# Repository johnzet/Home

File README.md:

# HomeAutomation
#test
#test master branch

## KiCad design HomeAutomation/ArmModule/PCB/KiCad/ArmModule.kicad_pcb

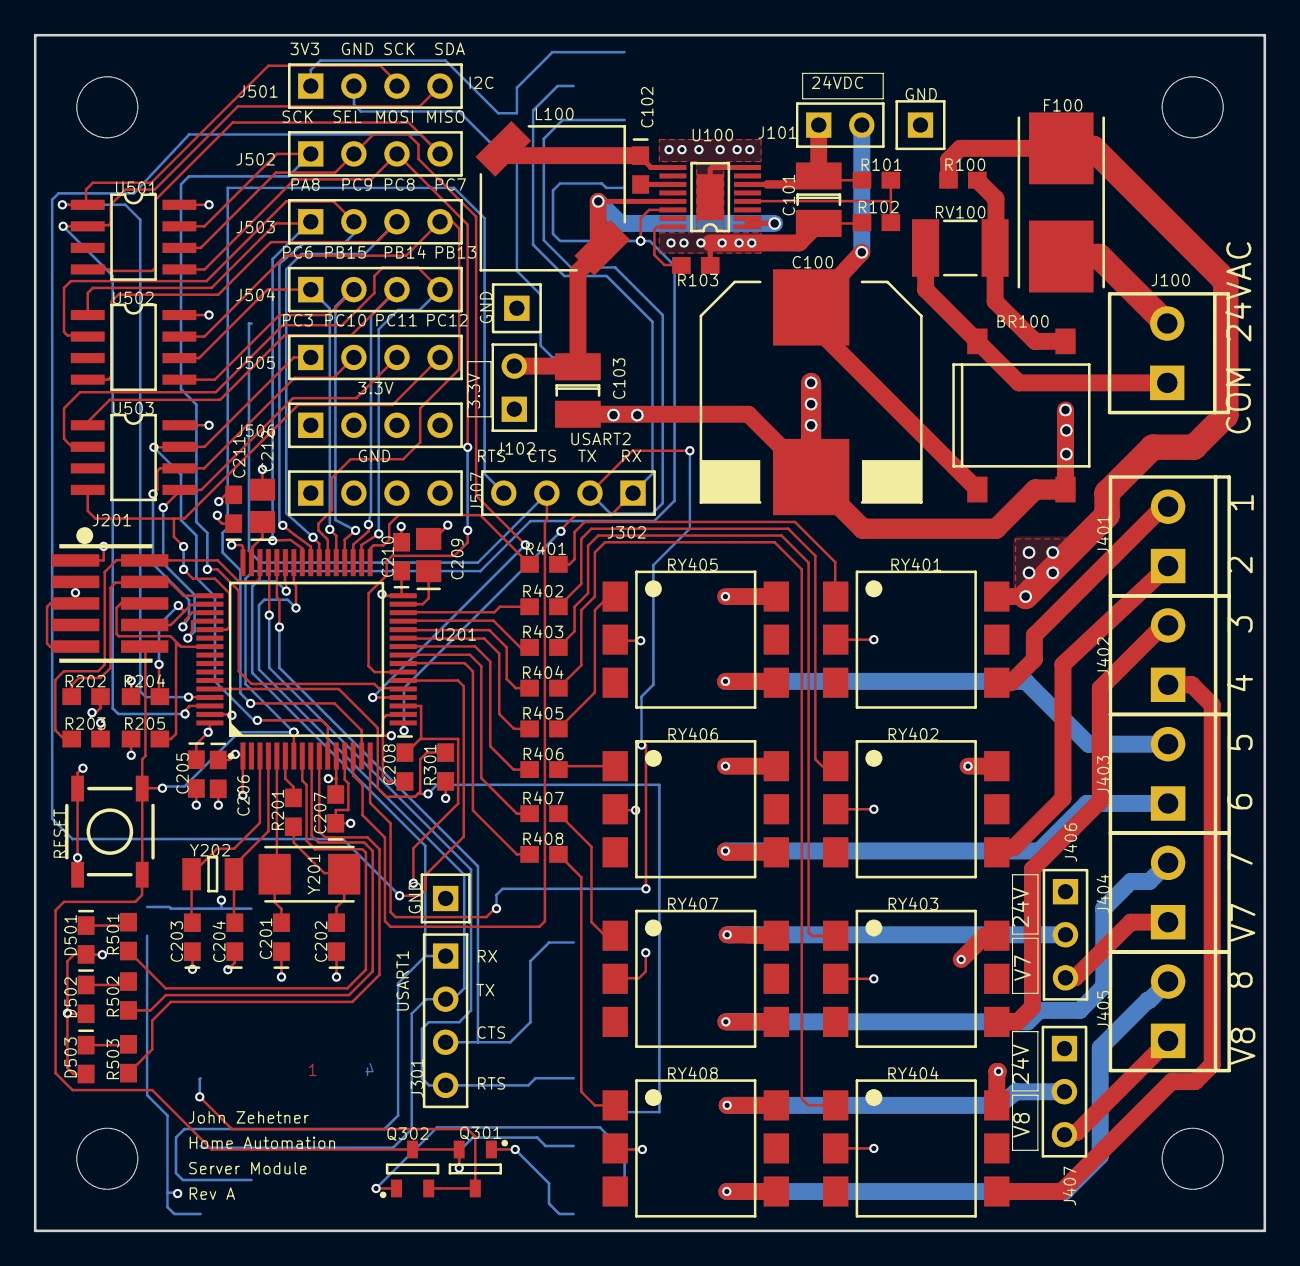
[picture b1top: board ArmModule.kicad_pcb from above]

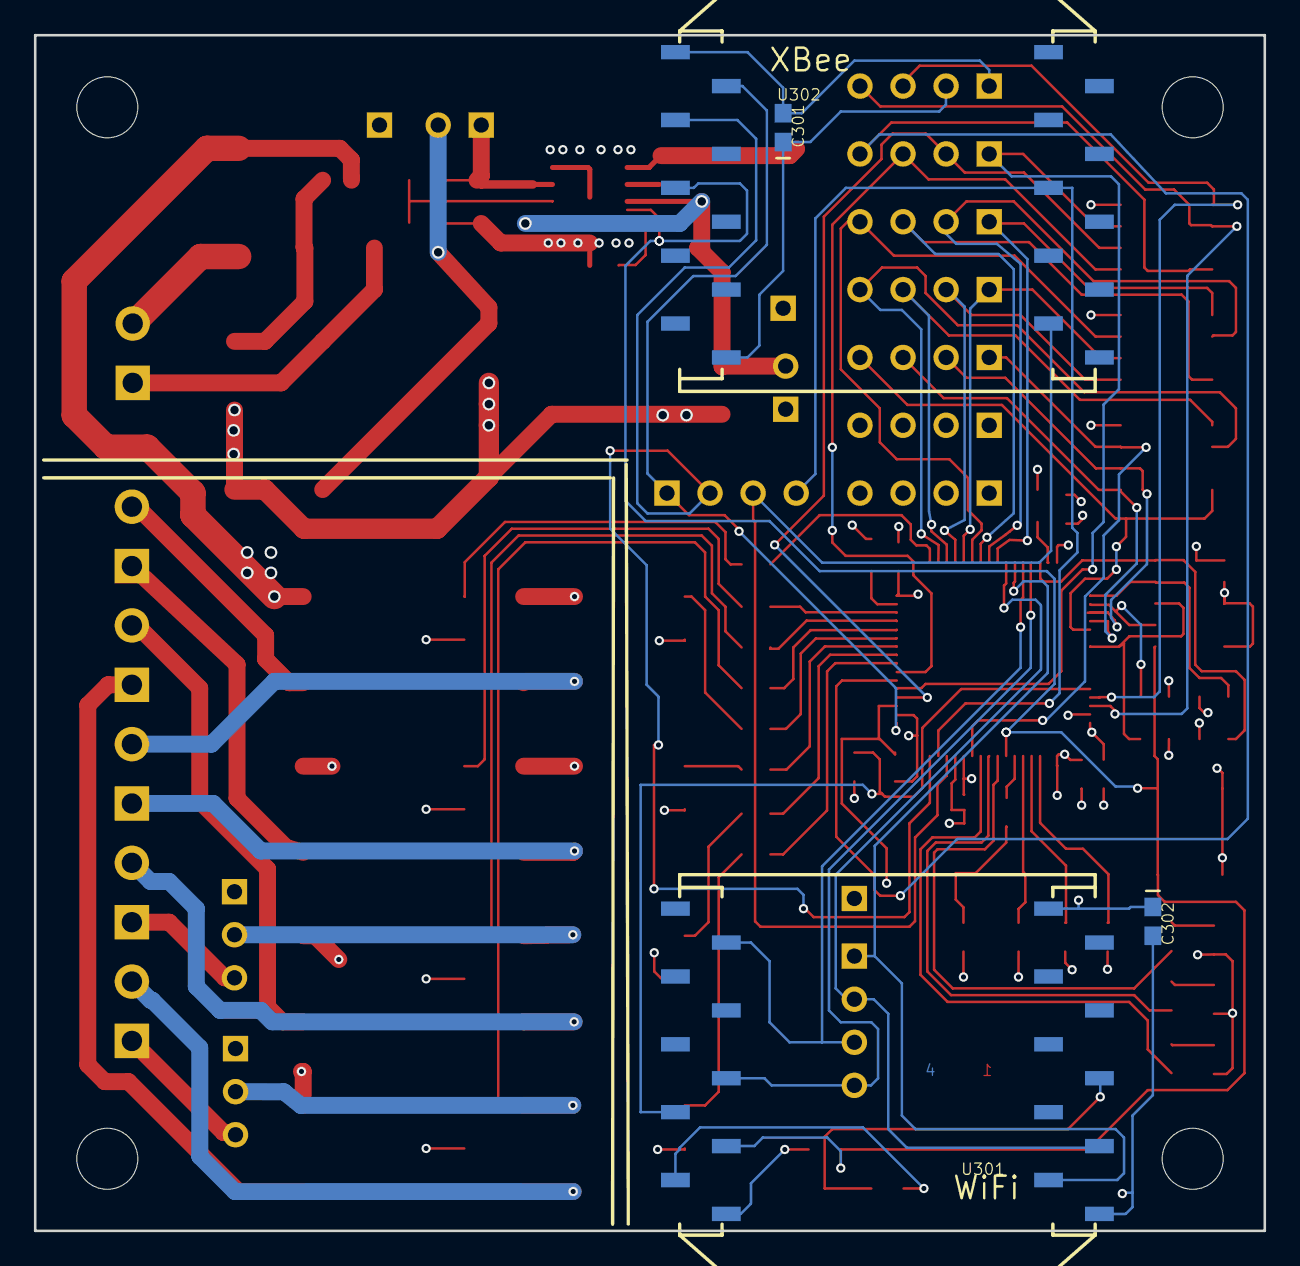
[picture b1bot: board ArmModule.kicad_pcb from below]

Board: 4 copper layers, 72.5 x 70.5 mm, 94 parts (4 on the bottom side), 89 nets.

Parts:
BR100: DF01S; Bridge_Rectifier
C100: 220uF 63V; Electro_Cap_H13
C101: 2.2u 100V; CAP_1210
C102: 0.22u; CAP_0603
C103: 22u; CAP_1210_C103
C201, C202: <= 26 pF; CAP_0603_C201
C203, C204: <= 5 pF; CAP_0603_C201
C205, C208: 100nF; CAP_0603_C205
C206: 100nF; CAP_0603_C206
C207, C210: 100nF; CAP_0603_C201
C209: 2.2uF; CAP_0805
C211: 100nF; CAP_0603_C211
C212: 2.2uF; CAP_0805_C212
C301: 100nF; CAP_0603_C301
C302: 100nF; CAP_0603_C302
D501: Red; DIO_0603
D502: Green; DIO_0603
D503: Blue; DIO_0603
F100: 63mA; Fuse_Holder
J100: HEADER1X2; SCREWTERMINAL-3.5MM-2
J101: JUMPER; HDR-1x2
J102: JUMPER; HDR-1x2_J102
J201: FTSH-105-01-L-DV
J301: HEADER1X4; HDR-1x4
J302: HEADER1X4; HDR-1x4_J302
J401, J402, J403, J404, J405: HEADER1X2; SCREWTERMINAL-3.5MM-2_J401
J406: HEADER1X3; HDR-1x3
J407: HEADER1X3; HDR-1x3_J407
J501, J502, J503, J504, J505, J506: HEADER1X4; HDR-1x4_J501
J507: HEADER1X4; HDR-1x4_J507
Keepout_1: 1; ROUTE_KEEPOUT_1
L100: 33uF; Panasonic_33uH
Q301: MOSFET_N; SOT23
Q302: MOSFET_P; SOT23_Q302
R100: 0; RES_0603
R101: 100K; RES_0603
R102, R103, R202, R203, R301: 10K; RES_0603_R102
R201: 765; RES_0603
R204, R205: 10K; RES_0603
R401, R402, R403, R404, R405, R406, R407, R408: 570; RES_0603
R501: 270; RES_0603_R102
R502: 62; RES_0603_R102
R503: 82; RES_0603_R102
RV100: VG181245U900; RES_1813
RY401, RY402, RY403, RY404, RY405, RY406, RY407, RY408: VO14642AABTR; SS_Relay
SW201: TAC_SWITCHSMD; TACTILE_SWITCH_SMD
TP501, TP503: GND; PIN1
TP502: GND; PIN1_TP502
U100: LT3990; MSOP-16EP
U201: STM32F405RG; QFP-64_12x12x0.5
U301: WiFi; XBEE-SMD
U302: XBee; XBEE-SMD_U302
U501, U502, U503: SRDA3.3-6; SOIC-8_150mil
UNK_HOLE_0: dummyfp0
UNK_HOLE_1: dummyfp1
UNK_HOLE_2: dummyfp2
UNK_HOLE_3: dummyfp3
Y201: 8MHz; ABM3
Y202: 32.768 KHz; 32.768_KHz_Crystal

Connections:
3V3: C205.1, C206.1, C207.1, C208.1, C210.1, C211.1, C301.1, C302.1, D501.2, D502.2, D503.2, J102.1, J201.1, J501.1, J506.1, J506.2, J506.3, J506.4, R202.2, R203.2, R204.2, R205.2, U201.1, U201.13, U201.19, U201.32, U201.48, U201.64, U301.1, U302.1
24VAC: F100.2, J406.1, J407.1, R100.2, RY401.6, RY402.6, RY403.6, RY404.6, RY405.6, RY406.6
24VDC: BR100.3, C100.2, J101.2
24V_COMM: BR100.2, J100.1, RV100.1
24V_in: F100.1, J100.2
A: J503.1, U201.41, U502.1
B: J503.2, U201.40, U502.2
BOOT0: R301.2, U201.60, U301.17
Blue_LED: R503.1, U201.10
C: J503.3, U201.39, U502.4
D: J503.4, U201.38, U502.7
E: J504.1, U201.37, U502.6
F: J504.2, U201.36, U502.5
G: J504.3, U201.35, U503.1
GND: BR100.4, C100.1, C101.2, C103.2, C201.1, C202.1, C203.1, C204.1, C205.2, C206.2, C207.2, C208.2, C209.2, C210.2, C211.2, C212.2, C301.2, C302.2, J201.3, J201.5, J201.9, J501.2, J507.1, J507.2, J507.3, J507.4, R102.1, R103.1, R301.1, RY401.2, RY402.2, RY403.2, RY404.2, RY405.2, RY406.2, RY407.2, RY408.2, SW201.1, SW201.2, TP501.1, TP502.1, TP503.1, U100.8, U100.17, U201.12, U201.18, U201.63, U301.10, U302.10, U501.8, U502.8, U503.8
Green_LED: R502.1, U201.9
H: J504.4, U201.34, U503.2
I: J505.1, U201.11, U503.7
I2C_SCK: J501.3, U201.61, U501.1
I2C_SDA: J501.4, U201.62, U501.2
J: J505.2, U201.51, U503.6
JTCK_SWDCLK: J201.4, R202.1, U201.49
JTDI: J201.8, R204.1, U201.50
JTDO: J201.6, R205.1, U201.55
JTMS_SWDIO: J201.2, R203.1, U201.46
K: J505.3, U201.52, U503.5
L: J505.4, U201.53, U503.4
Net_0: J401.2, RY401.4
Net_1: D502.1, R502.2
Net_2: R201.1, U201.6
Net_3: D503.1, R503.2
Net_4: J405.2, RY408.4
Net_5: C201.2, U201.5, Y201.2
Net_7: R402.1, RY402.1
Net_11: R403.1, RY403.1
Net_12: BR100.1, R100.1, RV100.2
Net_15: R404.1, RY404.1
Net_19: R405.1, RY405.1
Net_21: C204.2, U201.4, Y202.1
Net_22: C203.2, U201.3, Y202.2
Net_23: R406.1, RY406.1
Net_25: J401.1, RY402.4
Net_27: R407.1, RY407.1
Net_29: C212.1, U201.47
Net_31: C209.1, U201.31
Net_33: R408.1, RY408.1
Net_35: Q301.3, Q302.2, U301.5
Net_37: R401.1, RY401.1
Net_43: J404.2, RY407.4
Net_44: J403.1, RY406.4
Net_45: J403.2, RY405.4
Net_64: J402.2, RY403.4
Net_65: J402.1, RY404.4
Net_70: Q301.1, U301.20
Net_71: Q302.1, U301.19
Net_75: C101.1, J101.1, R101.2, U100.6
Net_76: C102.2, U100.11
Net_77: C103.1, J102.2, L100.2, U100.1, U100.2, U100.13
Net_78: R103.2, U100.16
Net_79: C102.1, L100.1, U100.9
Net_80: R101.1, R102.2, U100.4
Net_84: D501.1, R501.2
Net_85: J404.1, J406.3
Net_86: J405.1, J407.3
Net_87: J407.2, RY408.6
Net_88: J406.2, RY407.6
Net_98: C202.2, R201.2, Y201.1
RESET: J201.10, Q301.2, Q302.3, SW201.3, SW201.4, U100.14, U201.7, U301.18, U302.5
Red_LED: R501.1, U201.8
Relay1: R401.2, U201.33
Relay2: R402.2, U201.30
Relay3: R403.2, U201.29
Relay4: R404.2, U201.28
Relay5: R405.2, U201.27
Relay6: R406.2, U201.26
Relay7: R407.2, U201.25
Relay8: R408.2, U201.24
SPI_MISO: J502.4, U201.22, U501.4
SPI_MOSI: J502.3, U201.23, U501.5
SPI_SCK: J502.1, U201.21, U501.7
SPI_SEL: J502.2, U201.20, U501.6
UART1_CTS: J301.3, U201.44, U301.12
UART1_RTS: J301.4, U201.45, U301.16
UART1_RX: J301.1, U201.43, U301.2
UART1_TX: J301.2, U201.42, U301.3
UART2_CTS: J302.3, U201.14, U302.12
UART2_RTS: J302.4, U201.15, U302.16
UART2_RX: J302.1, U201.17, U302.2
UART2_TX: J302.2, U201.16, U302.3

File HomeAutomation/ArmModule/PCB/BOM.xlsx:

Stock | RefDes | Value | Pattern | Name | Voltage | SparkFun part # | DigiKey part # | Quantity Needed | Part No | Datasheet
1 | BR100 | DF01S | Bridge Rectifier | Bridge Rectifier |  |  | DF01S-TDICT-ND | 3
1 | C100 | 500uF 63V | Electro Cap H13 | CAP200RP |  |  | PCE3484CT-ND | 3
3 | C101 | 2.2u 100V | CAP_1210 | CAP_1210 | 100V |  | 490-6545-1-ND | 5
3 | C102 | 0.22u | CAP_0603 | CAP_0603 |  |  | 490-8017-1-ND | 5
3 | C103 | 22u | CAP_1210 | CAP_1206 |  |  | 490-5890-1-ND | 5
5 | C201, C202 | <= 26 pF | CAP_0603 | CAP_0603 | 50V |  | 490-1411-1-ND | 10
6 | C203, C204 | <= 5 pF | CAP_0603 | CAP_0603 | 50V |  | 490-10718-1-ND | 10
34 | C205, C206, C207, C208, C210, C211, C301, C302 | 100nF | CAP_0603 | CAP_0603 | 50V |  | 490-9732-1-ND | 50
5 | C209, C212 | 2.2uF | CAP_0805 | CAP_0805 | 50V |  | 490-3331-1-ND | 10
21 | D501 | Red | DIO_0603 | LED |  |  |  | 0
21 | D502 | Green | DIO_0603 | LED |  |  |  | 0
21 | D503 | Blue | DIO_0603 | LED |  |  |  | 0
1 | F100 | 62mA | Fuse Holder | FUSE |  |  | F3148TR-ND | 3
0 | J100, J401, J402, J403, J404 |  | SCREWTERMINAL-3.5MM-2 | Header1x2 |  |  |  | 1
 | J101, J102 |  | HDR-1x2 | JUMPER |  |  | WM50016-36-ND | 0
1 | J201 | FTSH-105-01-L-DV | FTSH-105-01-L-DV | FTSH-105-01-L-DV |  |  | SAM8799-ND | 3
 | J301, J302, J501, J502, J503, J504, J505, J506, J507 |  | HDR-1x4 | Header1x4 |  |  |  | 0
1 | L100 | 33uH | Panasonic 33uH | 33uH |  |  | PCD2447CT-ND | 3 | Panasonic ELL-8TP330MB
0 | Q301 |  | SOT23 | MOSFET_N |  |  | 568-6216-1-ND | 10
1 | Q302 |  | SOT23 | MOSFET_P |  |  | DMP3160LDICT-ND | 10
not used | R100 | 1 | RES_0603 | RES_0603 |  |  | 1276-4471-1-ND | 10
7 | R101,R103 | 100K | RES_0603 | RES_0603 |  |  | 1276-3486-1-ND | 10
86 | R102, R202, R203, R204, R205, R301 | 10K | RES_0603 | RES_0603 |  |  | 1276-3485-1-ND | 100
 | R201 | 765 | RES_0603 | RES_0603 |  |  | 1276-4471-1-ND | 10
94 | R401, R402, R403, R404, R405, R406, R407, R408 | 570 | RES_0603 | RES_0603 |  |  | 1276-4625-1-ND | 100
8 | R501 | 270 | RES_0603 | RES_0603 |  |  | 1276-4594-1-ND | 10
8 | R502 | 62 | RES_0603 | RES_0603 |  |  | 1276-4548-1-ND | 10
8 | R503 | 82 | RES_0603 | RES_0603 |  |  | 1276-4556-1-ND | 10
1 | RV100 | VG181245U900 | RES_1813 | Varistor |  |  | 478-9638-1-ND | 3
 | RY401, RY402, RY403, RY404, RY405, RY406, RY407, RY408 | VO14642AABTR | SS Relay | SS Relay |  |  | VO14642AABCT-ND | 3
 | SW201 | TAC_SWITCHSMD | TACTILE_SWITCH_SMD | RESET |  | COM-08720 |  | 0
 | TP501, TP502, TP503 |  | PIN1 | GND |  |  |  | 0
1 | U100 | LT3990 | MSOP-16EP | LT3990 |  |  | LT3990EMSE-3.3#PBF-ND | 3
1 | U201 | STM32F405RG | QFP-64/12x12x0.5 | STM32F405RG |  |  | 497-11767-ND | 3
 | U301 | WiFi | XBEE-SMD | XBEE-1B3 |  |  | PRT-10030 | 0
 | U302 | XBee | XBEE-SMD | XBEE-1B3 |  |  | PRT-10030 | 6
 | U501, U502, U503 | CM1213-06SM | SOIC-8EP/150mil | Input Protection |  |  | SRDA3.3-6.TBTCT-ND | 3
1 | Y201 | 8MHz | ABM3 | ABM3-8.000MHZ-D2Y-T |  |  | 535-10630-1-ND | 3 |  | http://www.iqdfrequencyproducts.com/products/details/22/
1 | Y202 | 32.768 KHz | 32.768 KHz Crystal | 32.768 KHz Crystal |  |  | 535-12943-1-ND | 3 |  | http://www.abracon.com/Resonators/ABS07-LR.pdf

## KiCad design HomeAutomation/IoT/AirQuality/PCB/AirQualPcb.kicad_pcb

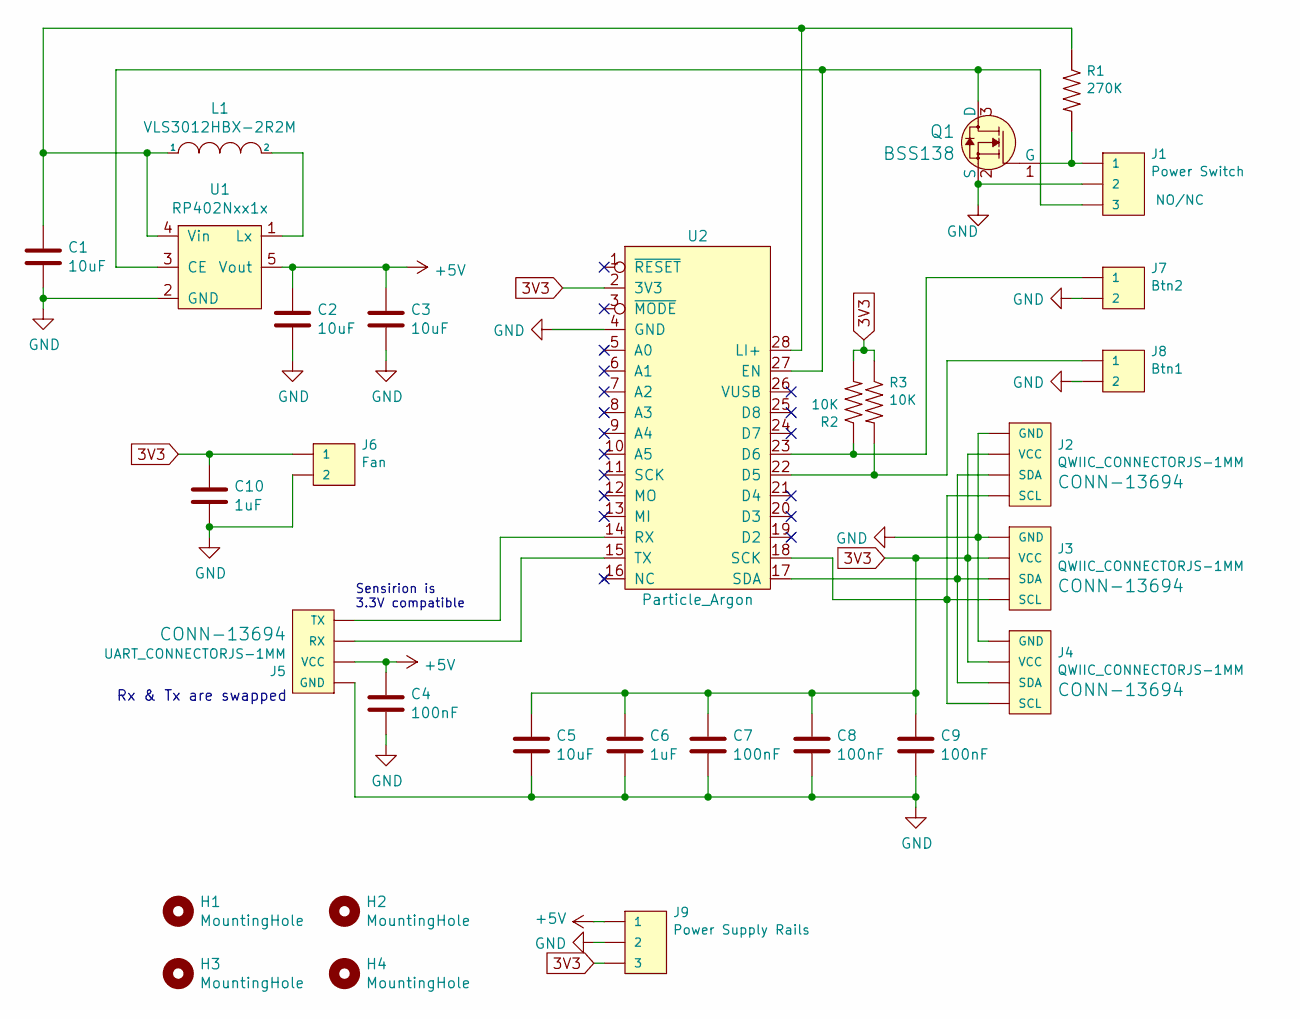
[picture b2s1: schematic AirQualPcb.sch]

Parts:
C1, C2, C3, C5: 10uF; 0603
C4, C7, C8, C9: 100nF; 0603
C6, C10: 1uF; 0603
H1, H2, H3, H4: MountingHole; MountingHole_3.2mm_M3
J1: Power Switch; 1X03
J2, J3, J4: QWIIC_CONNECTORJS-1MM; JST_SH_SM04B-SRSS-TB_1x04-1MP_P1.00mm_Horizontal
J5: UART_CONNECTORJS-1MM; 1X04_1MM_RA
J6: Fan; 1X02
J7: Btn2; 1X02
J8: Btn1; 1X02
J9: Power Supply Rails; 1X03
L1: VLS3012HBX-2R2M‎; VLS3012HBX
Q1: BSS138; SOT-23-3; MPN BSS138; Digi-Key_PN BSS138CT-ND
R1: 270K; R_0603_1608Metric
R2, R3: 10K; R_0603_1608Metric
U1: RP402Nxx1x; SOT-23-5
U2: Particle_Argon; ParticleArgon

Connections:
3V3: C5.1, C6.1, C7.1, C8.1, C9.1, C10.1, J2.2 (VCC), J3.2 (VCC), J4.2 (VCC), J6.1, J9.3, R2.2, R3.1, U2.2 (3V3)
+5V: C2.1, C3.1, C4.1, J5.2 (VCC), J9.1, U1.5 (Vout)
GND: C1.2, C2.2, C3.2, C4.2, C5.2, C6.2, C7.2, C8.2, C9.2, C10.2, J1.2, J2.1 (GND), J3.1 (GND), J4.1 (GND), J5.1 (GND), J6.2, J7.2, J8.2, J9.2, Q1.2 (S), U1.2 (GND), U2.4 (GND)
unnamed: C1.1, L1.1, R1.1, U1.4 (Vin), U2.28 (LI+)
unnamed: J1.1, Q1.1 (G), R1.2
unnamed: J1.3, Q1.3 (D), U1.3 (CE), U2.27 (EN)
unnamed: J2.3 (SDA), J3.3 (SDA), J4.3 (SDA), U2.17 (SDA)
unnamed: J2.4 (SCL), J3.4 (SCL), J4.4 (SCL), U2.18 (SCK)
unnamed: J5.3 (RX), U2.15 (TX)
unnamed: J5.4 (TX), U2.14 (RX)
unnamed: J7.1, R2.1, U2.23 (D6)
unnamed: J8.1, R3.2, U2.22 (D5)
unnamed: L1.2, U1.1 (Lx)

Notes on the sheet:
Rx & Tx are swapped
Sensirion is 3.3V compatible

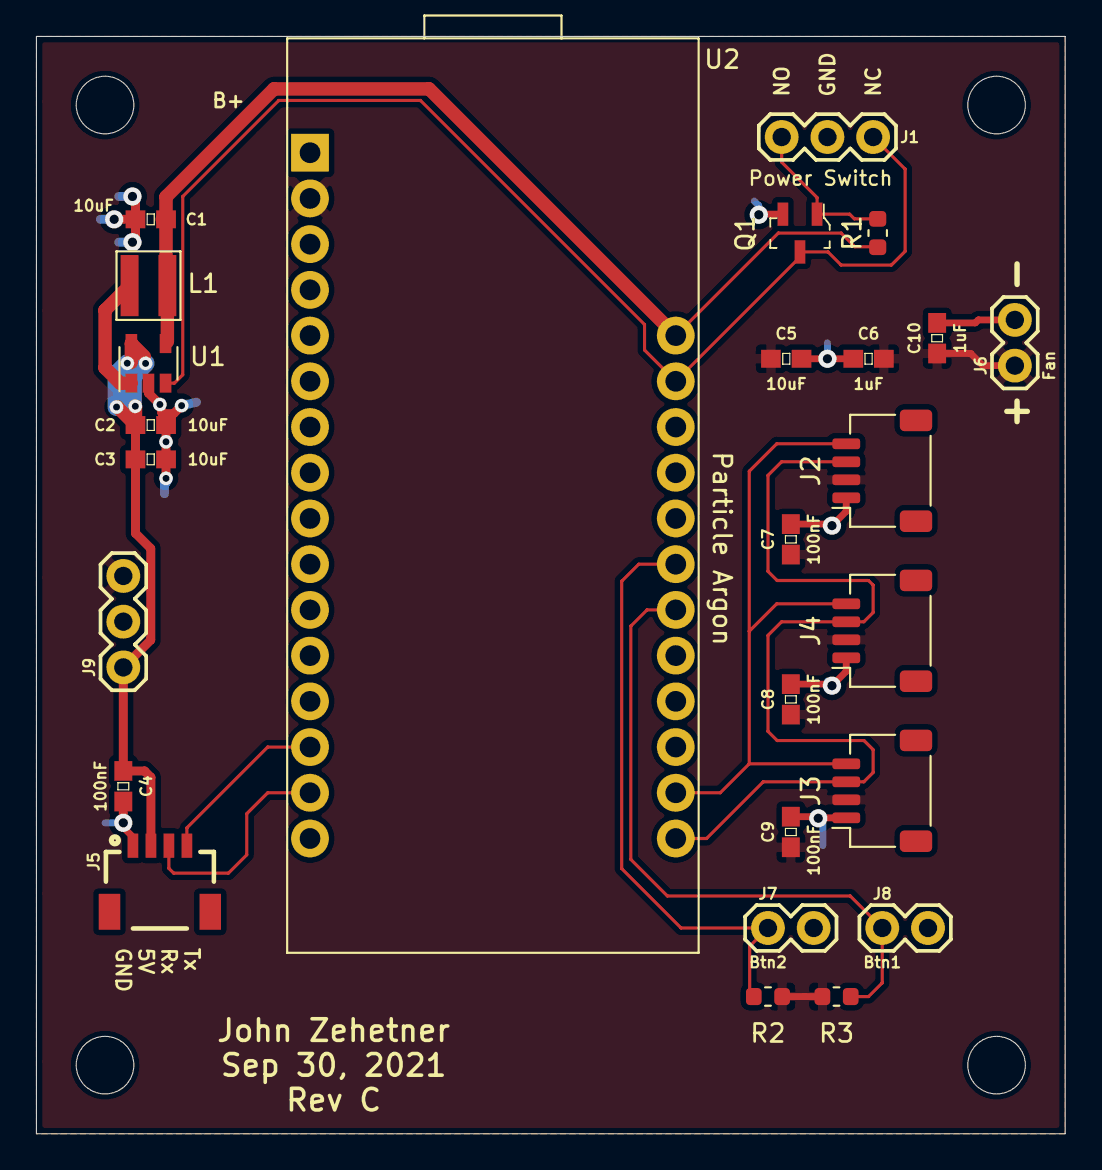
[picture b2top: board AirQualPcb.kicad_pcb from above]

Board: 2 copper layers, 57.2 x 61.0 mm, 30 parts (0 on the bottom side), 13 nets.

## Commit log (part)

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2016-12-04 initial checkin
2016-12-04 add docs
2016-12-04 add esp8266 tree
2016-12-13 Initial post design
2017-01-08 migrate to tomcat 8
2017-07-18 parameterize config server ip address
2017-07-18 parameterize ip address for firmware pusher
2017-07-18 Fix active sensor count
2017-07-19 Add common config file
2017-07-19 project file
2017-07-22 Add taskYIELD() in TXE waits + static analyzer warnings
2017-07-23 Initial checkin of Angular client and server
2017-08-03 Add basic page structure and move to angular bootstrap
2017-08-03 Deck Blender files which rendered first YouTube video
2017-08-03 gitignore patterns
2017-08-04 test
2017-08-14 single news reader card
2017-08-14 add an accordion
2017-08-14 news reader is basically working
2017-08-14 initial checkin of flash messages
2017-08-14 convert some printfs to MessageList
2017-08-14 minor changes to flash
2017-08-14 Add the FreeRTOS manual
2017-08-16 Set tasks to equal priority so taskYIELD() works better.
2017-08-18 Misc
2017-08-28 Fixed firmware wireless push
2017-09-02 More firmware pusher changes
2017-09-02 Add threads.js (not right, though)
2017-09-05 Set absolute path to hex file
2017-09-05 Fix priority values from an STM32F4 example
2017-09-05 Add packet reassembly plus a received packet queue
2017-09-05 DS_Store files
2017-09-09 Implement home tab as an accordion. Also add Accuweather.
2017-09-09 Charts starting to appear
2017-09-15 Set some db columns as enums
2017-09-15 Add db erase/populate tests
2017-09-16 Add a base deck blender file for 3d printing
2017-09-17 Periodic save
2017-09-17 Chart improvements - fetching all sensors, junit test to populate the db.
2017-09-18 Add a rest method to get teh most recent sample of each sensor
2017-09-18 Add deck textures for 3d rendering
2017-10-01 incremental
2017-10-15 Some custom repo work
2017-10-22 First pass at splitting main and MainTask
2018-06-06 periodic checkin
2018-07-08 Move to Angular 6 and MAterial. Add main menu as sive nav.
2018-07-08 Services compiled
2018-07-23 Nav Pane in angular 4, Some integration tests working in jboss and arquilian
2020-05-29 Various stuff - Some really old
2020-05-29 reaally old stuff
2020-05-29 really old stuff
2020-05-29 remove unncessary files
2020-05-30 break into include and src directories
2020-05-30 add src and include
2020-05-30 vs studio project
2020-05-30 move includes to src directory
2020-08-15 initial for Weather project
2020-08-15 misc and excess
2020-08-15 rm extra
2020-08-15 magnetometer works
2020-08-15 tweak sampling and filtering
2020-08-15 Added BME280 sensor
2020-10-31 bluetooth works with hard coded values
2020-11-08 Added electronics enclosure
2020-11-08 add anemometer cup
2020-11-08 enclosure looks god, anemometer first pass OK
2020-11-08 no message
2020-11-11 Anemometer
2020-11-15 replaced dowel with printed arms
2020-11-22 Finished enclosure
2020-11-24 Add fillet to anem cup
2020-11-24 Minor display tweaks
2020-11-28 Change batt level to percentage and add to bluetooth
2020-11-28 Add a couple directories
2020-11-28 fix 360 degree roll over
2020-12-06 Anemometer calibrator initial checking
2020-12-08 fix threading with broadcasts
2020-12-19 No checkin for a long while
2020-12-28 AirQual enclosure has parts positioned, PCB is just an initial drawing
2020-12-29 PCB laid-out. About to start tracks.
2020-12-29 Board mostly done
2020-12-30 About to start cutting holes in enclosure
2020-12-31 Switch to the internal battery voltage sensor
2021-01-02 Add a fan power connector
2021-01-02 Set M3 screw size in dd
2021-01-03 Cut holes for fan with new procedure
2021-01-03 Cut holes for LCD and rocker switch
2021-01-04 Enclosure is Done enough
2021-01-06 a couple last minute changes before sending to fab
2021-01-06 Rearrange firmware files
2021-01-09 Add unknown characteristics back in
2021-01-12 Making progress with cutting holes and not creating circular dependencies
2021-01-12 Good check point in cutting holes. Lower is done, started on top.
2021-01-12 Minor changes
2021-01-13 Holes are all cut, need to add fillets and double check
2021-01-14 Update the test piece
2021-01-15 Just about to start fillets.
2021-01-15 Added alignment tabs and fillets.
2021-01-24 Just got the debugger working
2021-01-27 PCB: change Argon footprint, direct-connect Sensirion, add button connectors
2021-01-27 Minor enclosure changes
2021-01-27 Minor firmware changes
2021-01-30 initial copy from svn
2021-08-01 directory rearrange and small mods to AirQual
2021-09-30 Fix power supply enable line
2021-09-30 firmware sensor tweaks
2021-10-06 Add a hole for the page pushbutton
2021-11-06 add mqtt publish and subscribe of outdoor sensor 1
2021-11-21 outdoor sensor mqtt changes
2021-11-21 AirQual changes for basic outdoor mqtt
2021-11-21 rm duplicate files
2022-05-26 add outdoor temp mqtt, increase outdoor sensor sleep time
2023-02-09 forgot to commit
